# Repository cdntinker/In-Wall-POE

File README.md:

Designed to fit inside of Wiremold surface mount boxes.

Inspired by the EAP235-wall wireless access point which has pass-through PoE.  I have a little receiver for my weather station that connects to the network via WiFi & is powered by a USB charger.

Center hole, initially,  exists to make room for the Ethernet cable feeding the EAP235.  Of course, it can also allow for the cables to feed into the wall.

J1 supplies 5V output at up to 7W and can have a USB-A pigtail connected to feed devices outside the box.

The outline on layer User1 is the internals of a typical Wiremold surface box.

> [!NOTE]
> The outline on layer User2 in the board view is a fairly accurate representation of an Ethernet plug in position in the jack.
> 
> The outline on layer User3 is a fairly accurate representation of an Ethernet plug in the back of the EAP235.

> [!TIP]
> Actual board should fit in ANY North American box.

> [!TIP]
> The PoE module in use is available in 3v3, 5v0 and 12v versions.
> So, this board could also be used to supply those voltages.

> [!NOTE]
> See notations in the schematic and refer to the datasheet for information about resistors R1-R3.

2024/01/22: upgraded from the overkill Ethernet jack to a better fit plus magnetics...

2024/02/13: Assembled first board
* No smoke, but not producing output properly...
  * So far, suspect it needs more of a load.  Will test once I find a USB-A pigtail.
* Need to change footprint of L1 to something easier to hand-solder & move C1 a little to the left to make assembly easier.

2024/02/15: Tested successfully
* Definitely needs minimum load.
  * Added 2x 470 ohm resistors in parallel at R3 (Now Rl1 & Rl2)
* ~~Does not seem to reliably keep voltage under much load.~~
  * ~~Possibly because of knock-off module?  Must get Silvertel modules & test...~~
* Modified L1 footprint, moved C1 & added an extra load resistor footprint.  All to ease assembly.

2024/02/22: Tested with actual Silvertel module AND no longer trust Chinese USB testers
* Received Silvertel module from Mouser & assembled another board.
  * EXACTLY the same results.
* **THEN**, Just for giggles, actually measured the output with my regular meter (Uni-T UT61e)
  * Well...  That's interesting.  UT61e says the output is a nice stable 5V (give or take ~0.03V)
  * Yet the load tester AND an inline USB tester both show severe voltage drop as current goes up.

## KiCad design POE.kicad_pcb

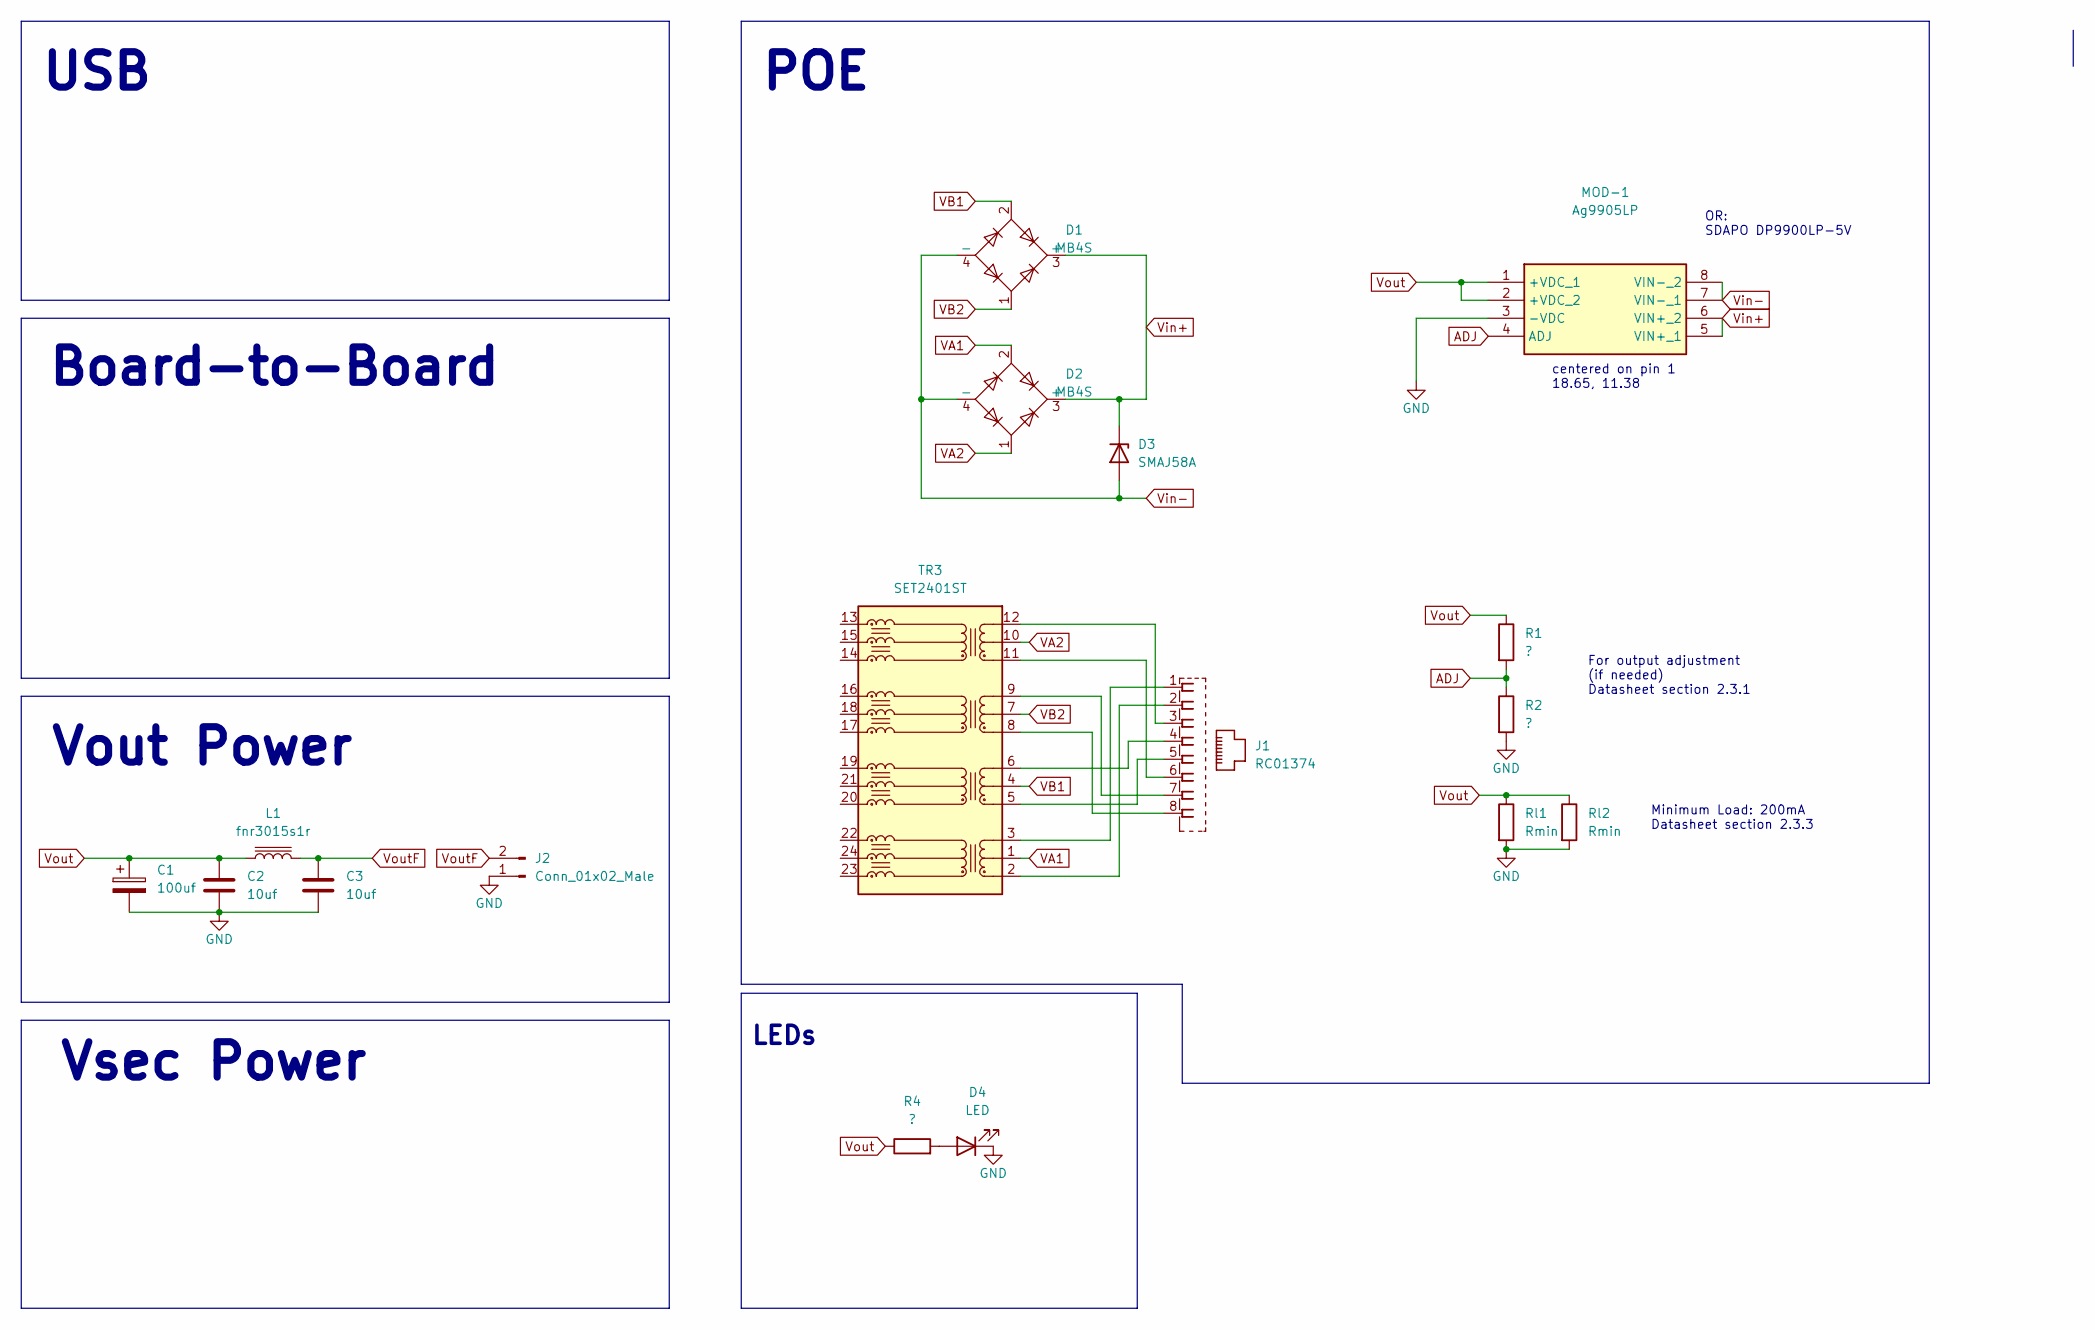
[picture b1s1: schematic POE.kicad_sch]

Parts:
C1: 100uf; CP_Elec_6.3x5.4; LCSC C7442639
C2, C3: 10uf; C_0805_2012Metric; LCSC C15850
D1, D2: MB4S; TO-269AA; LCSC C20612967
D3: SMAJ58A; D_SMA; LCSC C280379
D4: LED; LED_0805_2012Metric
J1: RC01374; LCSC C385834
J2: Conn_01x02_Male; PinHeader_1x02_P2.54mm_Horizontal
L1: fnr3015s1r; fnr3015s; LCSC C167746
MOD-1: Ag9905LP; Ag9912LP; Manufacturer_Part_Number Ag9905LP; LCSC C5380108
R1, R2, R4: ?; R_0805_2012Metric_Pad1.20x1.40mm_HandSolder
Rl1, Rl2: Rmin; R_0805_2012Metric_Pad1.20x1.40mm_HandSolder
TR3: SET2401ST; Eth_Magnetics (1.0); LCSC C7603464

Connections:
ADJ: MOD-1.4 (ADJ), R1.2, R2.1
GND: C1.2, C2.2, C3.2, D4.1 (K), J2.1, MOD-1.3 (-VDC), R2.2, Rl1.2, Rl2.2
unnamed: D4.2 (A), R4.2
unnamed: J1.1, TR3.3 (TD1-)
unnamed: J1.2, TR3.2 (TD1+)
unnamed: J1.3, TR3.12 (TD4-)
unnamed: J1.4, TR3.6 (TD2-)
unnamed: J1.5, TR3.5 (TD2+)
unnamed: J1.6, TR3.11 (TD4+)
unnamed: J1.7, TR3.9 (TD3-)
unnamed: J1.8, TR3.8 (TD3+)
VA1: D2.2, TR3.1 (TCT1)
VA2: D2.1, TR3.10 (TCT4)
VB1: D1.2, TR3.4 (TCT2)
VB2: D1.1, TR3.7 (TCT3)
Vin+: D1.3 (+), D2.3 (+), D3.1 (K), MOD-1.5 (VIN+_1), MOD-1.6 (VIN+_2)
Vin-: D1.4 (-), D2.4 (-), D3.2 (A), MOD-1.7 (VIN-_1), MOD-1.8 (VIN-_2)
Vout: C1.1, C2.1, L1.1, MOD-1.1 (+VDC_1), MOD-1.2 (+VDC_2), R1.1, R4.1, Rl1.1, Rl2.1
VoutF: C3.1, J2.2, L1.2

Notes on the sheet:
Vsec Power
Vout Power
OR: SDAPO DP9900LP-5V
USB
centered on pin 1 18.65, 11.38
Board-to-Board
For output adjustment (if needed) Datasheet section 2.3.1
POE
Minimum Load: 200mA Datasheet section 2.3.3
LEDs

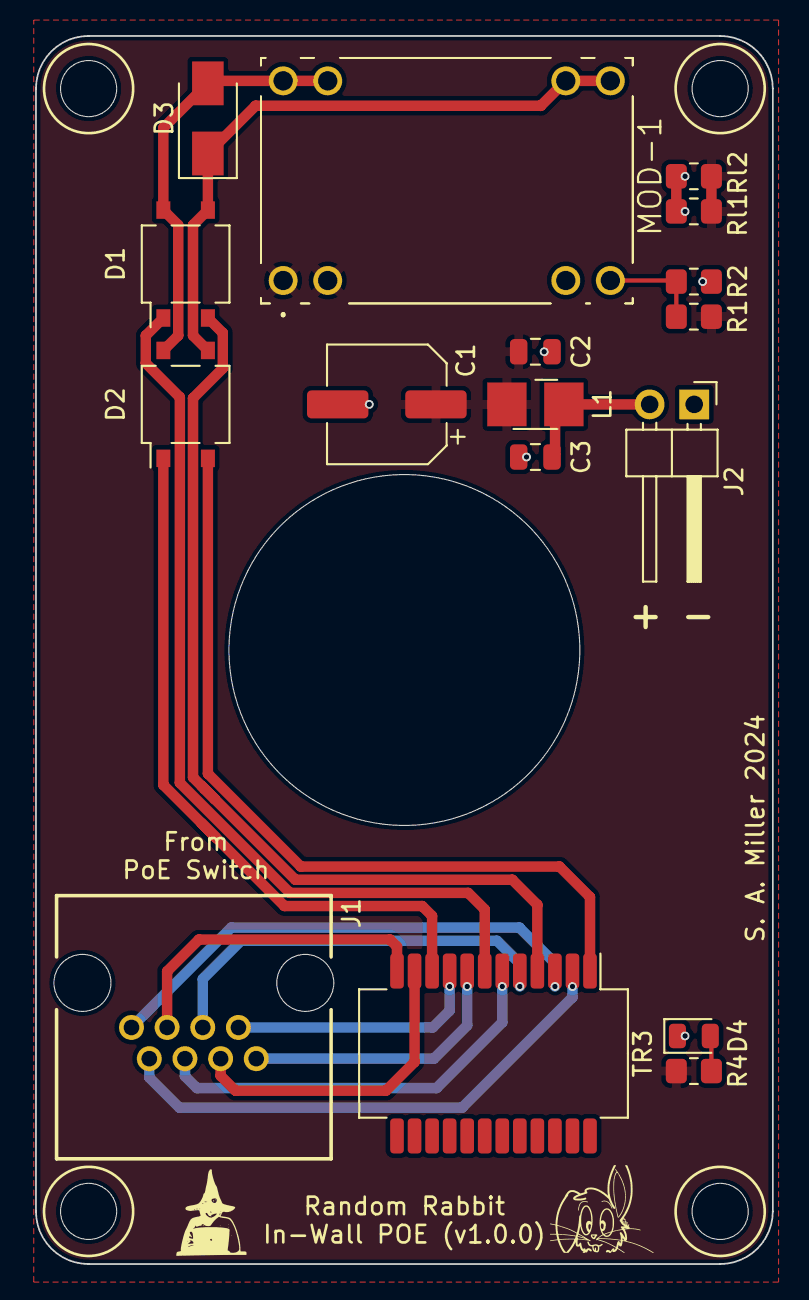
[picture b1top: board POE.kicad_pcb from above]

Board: 2 copper layers, 42.0 x 70.0 mm, 17 parts (0 on the bottom side), 19 nets.

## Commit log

2024-01-19 Some tweaking and explanation(s)
2024-01-19 Added adjustment & minLoad resistors
2024-01-23 upgraded from the overkill Ethernet jack to a better fit plus magnetics
2024-01-23 Addes a 3D nodel & renders
2024-01-23 trying to fix gitignore
2024-01-27 Some layout rework...
2024-02-01 Improved Vout filtering
2024-02-01 foorprint improvements & parts selections...
2024-02-01 Prepping for possible first build...
2024-02-01 gerbers produced, boards & parts ordered... (w/slow-boat shipping...)
2024-02-14 Thoughts after first assembly
2024-02-15 Post-test thoughts & adjustments.
2024-02-23 more testing notes
2024-03-09 bye bye bloody wrl files
